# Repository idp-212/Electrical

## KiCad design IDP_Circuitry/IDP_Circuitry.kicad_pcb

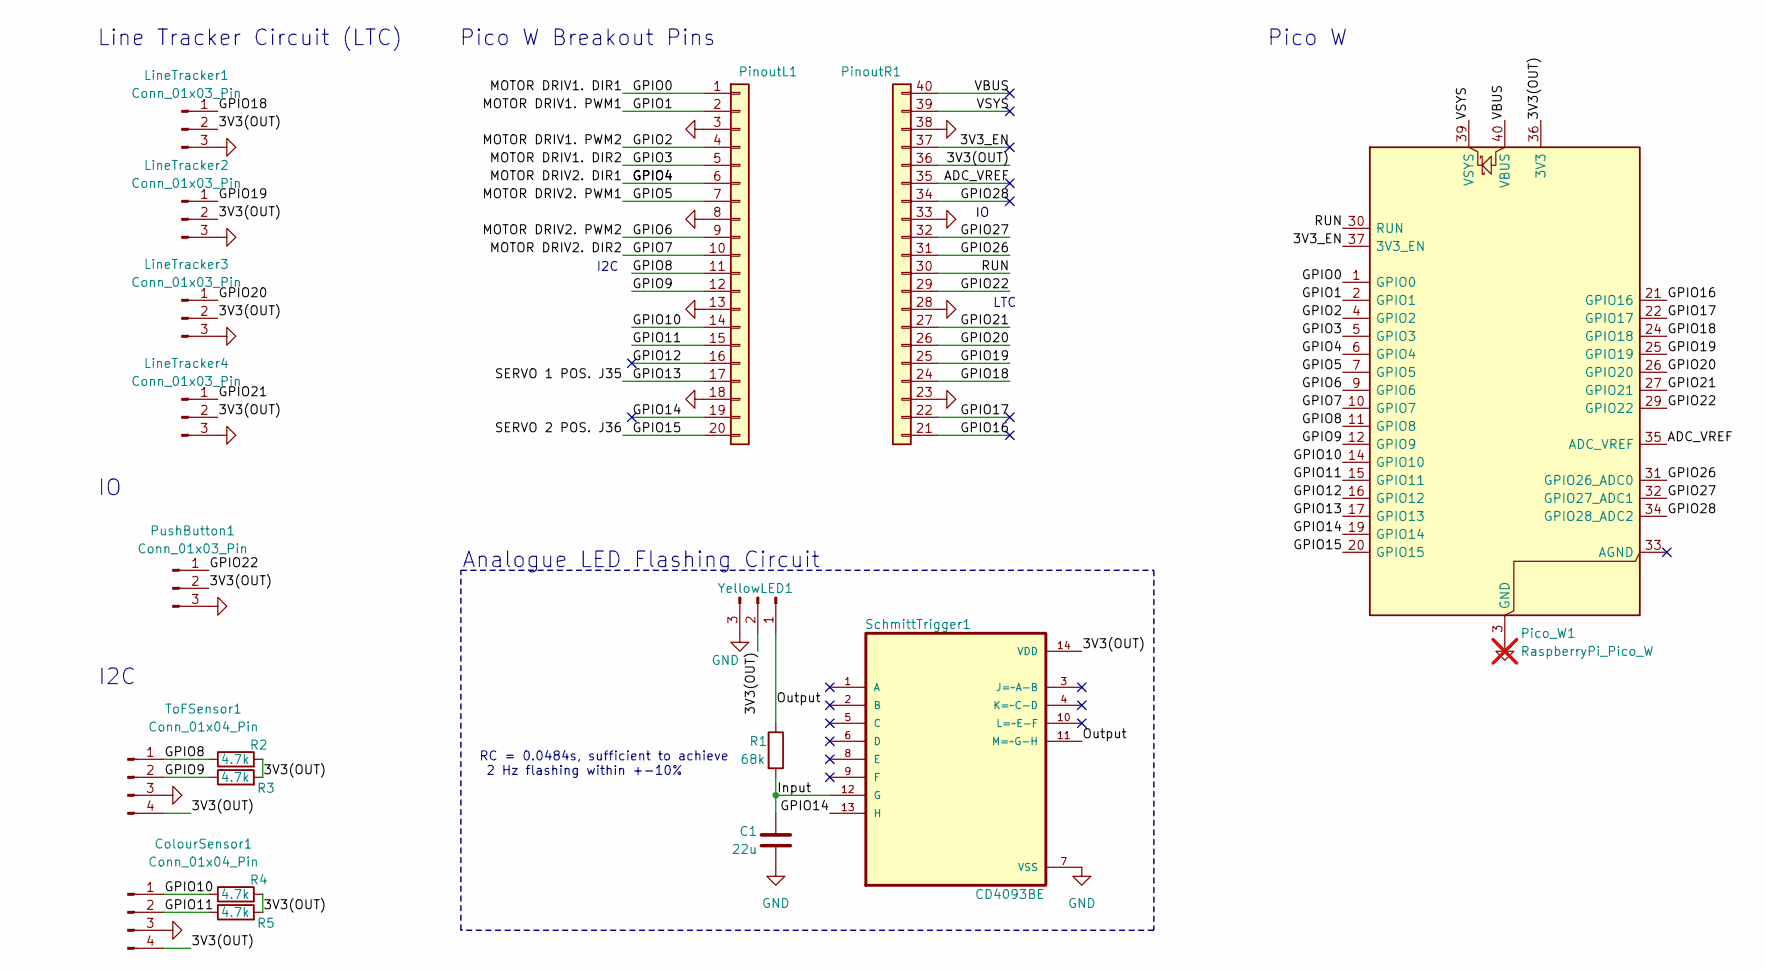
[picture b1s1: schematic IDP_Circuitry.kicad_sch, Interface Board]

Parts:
C1: 22u; C_Radial_D4.0mm_H5.0mm_P1.50mm
ColourSensor1: Conn_01x04_Pin; PinSocket_1x04_P2.54mm_Vertical
LineTracker1, LineTracker2, LineTracker3, LineTracker4: Conn_01x03_Pin; PinSocket_1x03_P2.54mm_Vertical
Pico_W1: RaspberryPi_Pico_W; RaspberryPi_Pico_Common_THT
PinoutL1: Conn_01x20; PinHeader_1x20_P2.54mm_Vertical
PinoutR1: Conn_01x20; PinHeader_1x20_P2.54mm_Vertical_Flipped_21-40
PushButton1: Conn_01x03_Pin; PinSocket_1x03_P2.54mm_Vertical
R1: 68k; R_Axial_DIN0204_L3.6mm_D1.6mm_P2.54mm_Vertical
R2, R3, R4, R5: 4.7k; R_Axial_DIN0204_L3.6mm_D1.6mm_P2.54mm_Vertical
SchmittTrigger1: CD4093BE; DIP794W45P254L1969H508Q14
ToFSensor1: Conn_01x04_Pin; PinSocket_1x04_P2.54mm_Vertical
YellowLED1: Conn_01x03_Pin; PinSocket_1x03_P2.54mm_Vertical

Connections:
/3V3(OUT): ColourSensor1.4, LineTracker1.2, LineTracker2.2, LineTracker3.2, LineTracker4.2, Pico_W1.36 (3V3), PinoutR1.36 (Pin_5), PushButton1.2, R2.2, R3.2, R4.2, R5.2, SchmittTrigger1.14 (VDD), ToFSensor1.4, YellowLED1.2
/3V3_EN: Pico_W1.37 (3V3_EN), PinoutR1.37 (Pin_4)
/ADC_VREF: Pico_W1.35 (ADC_VREF), PinoutR1.35 (Pin_6)
/GPIO0: Pico_W1.1 (GPIO0), PinoutL1.1
/GPIO1: Pico_W1.2 (GPIO1), PinoutL1.2
/GPIO2: Pico_W1.4 (GPIO2), PinoutL1.4
/GPIO3: Pico_W1.5 (GPIO3), PinoutL1.5
/GPIO5: Pico_W1.7 (GPIO5), PinoutL1.7
/GPIO6: Pico_W1.9 (GPIO6), PinoutL1.9
/GPIO7: Pico_W1.10 (GPIO7), PinoutL1.10
/GPIO8: Pico_W1.11 (GPIO8), PinoutL1.11, R2.1, ToFSensor1.1
/GPIO9: Pico_W1.12 (GPIO9), PinoutL1.12, R3.1, ToFSensor1.2
/GPIO10: ColourSensor1.1, Pico_W1.14 (GPIO10), PinoutL1.14, R4.1
/GPIO11: ColourSensor1.2, Pico_W1.15 (GPIO11), PinoutL1.15, R5.1
/GPIO12: Pico_W1.16 (GPIO12), PinoutL1.16
/GPIO13: Pico_W1.17 (GPIO13), PinoutL1.17
/GPIO14: Pico_W1.19 (GPIO14), PinoutL1.19, SchmittTrigger1.13 (H)
/GPIO15: Pico_W1.20 (GPIO15), PinoutL1.20
/GPIO16: Pico_W1.21 (GPIO16), PinoutR1.21 (Pin_20)
/GPIO17: Pico_W1.22 (GPIO17), PinoutR1.22 (Pin_19)
/GPIO18: LineTracker1.1, Pico_W1.24 (GPIO18), PinoutR1.24 (Pin_17)
/GPIO19: LineTracker2.1, Pico_W1.25 (GPIO19), PinoutR1.25 (Pin_16)
/GPIO20: LineTracker3.1, Pico_W1.26 (GPIO20), PinoutR1.26 (Pin_15)
/GPIO21: LineTracker4.1, Pico_W1.27 (GPIO21), PinoutR1.27 (Pin_14)
/GPIO22: Pico_W1.29 (GPIO22), PinoutR1.29 (Pin_12), PushButton1.1
/GPIO26: Pico_W1.31 (GPIO26_ADC0), PinoutR1.31 (Pin_10)
/GPIO27: Pico_W1.32 (GPIO27_ADC1), PinoutR1.32 (Pin_9)
/GPIO28: Pico_W1.34 (GPIO28_ADC2), PinoutR1.34 (Pin_7)
/Input: C1.1, R1.2, SchmittTrigger1.12 (G)
/MOTOR DRIV2. DIR1: Pico_W1.6 (GPIO4), PinoutL1.6
/Output: R1.1, SchmittTrigger1.11 (M=~G-H), YellowLED1.1
/RUN: Pico_W1.30 (RUN), PinoutR1.30 (Pin_11)
/VBUS: Pico_W1.40 (VBUS), PinoutR1.40 (Pin_1)
/VSYS: Pico_W1.39 (VSYS), PinoutR1.39 (Pin_2)
GND: C1.2, ColourSensor1.3, LineTracker1.3, LineTracker2.3, LineTracker3.3, LineTracker4.3, Pico_W1.3 (GND), Pico_W1.8 (GND), Pico_W1.13 (GND), Pico_W1.18 (GND), Pico_W1.23 (GND), Pico_W1.28 (GND), Pico_W1.38 (GND), PinoutL1.3, PinoutL1.8, PinoutL1.13, PinoutL1.18, PinoutR1.23 (Pin_18), PinoutR1.28 (Pin_13), PinoutR1.33 (Pin_8), PinoutR1.38 (Pin_3), PushButton1.3, SchmittTrigger1.7 (VSS), ToFSensor1.3, YellowLED1.3

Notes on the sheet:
Pico W Breakout Pins
RC = 0.0484s, sufficient to achieve 2 Hz flashing within +-10%
Analogue LED Flashing Circuit
LTC
Pico W
Line Tracker Circuit (LTC)
I2C

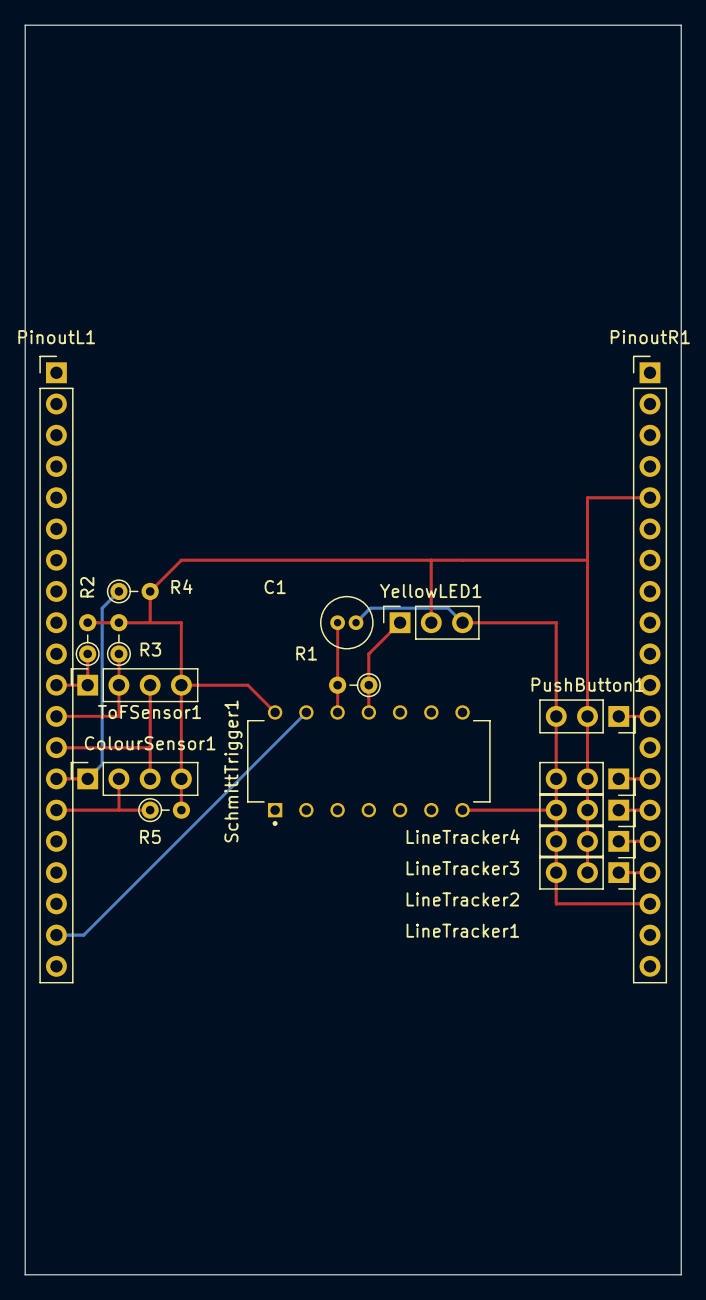
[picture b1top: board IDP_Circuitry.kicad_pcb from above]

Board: 2 copper layers, 53.3 x 101.6 mm, 17 parts (0 on the bottom side), 14 nets.

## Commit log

2025-02-23 Added getting started code
2025-02-25 ToF and ultrasonic sensor programs
2025-02-26 Added eagle libraries folder
2025-02-26 Added raspberry pico and schmitt trigger libraries
2025-02-26 Added circuit design for LED flasher
2025-02-27 Corrected resistor values, changed schmitt NAND gate used, and adjusted schematic to fit all components on the same sheet
2025-03-04 added schematics for the pinout board, line tracking sensors and added a button to the LED flasher
2025-03-06 added all footprints, added libraryIDP for flipped pin header schematic
2025-03-11 updated pcb, need to change footprint to make the ic compatible with the pinout board holes
2025-03-12 completed updates schematic and wired all components on the pcb. Minor tweaks likely necessary, but overall complete
2025-03-13 final commit, completed schematic/pcb and fully labelled
2025-03-19 added pdfs for the schematic and pcb
